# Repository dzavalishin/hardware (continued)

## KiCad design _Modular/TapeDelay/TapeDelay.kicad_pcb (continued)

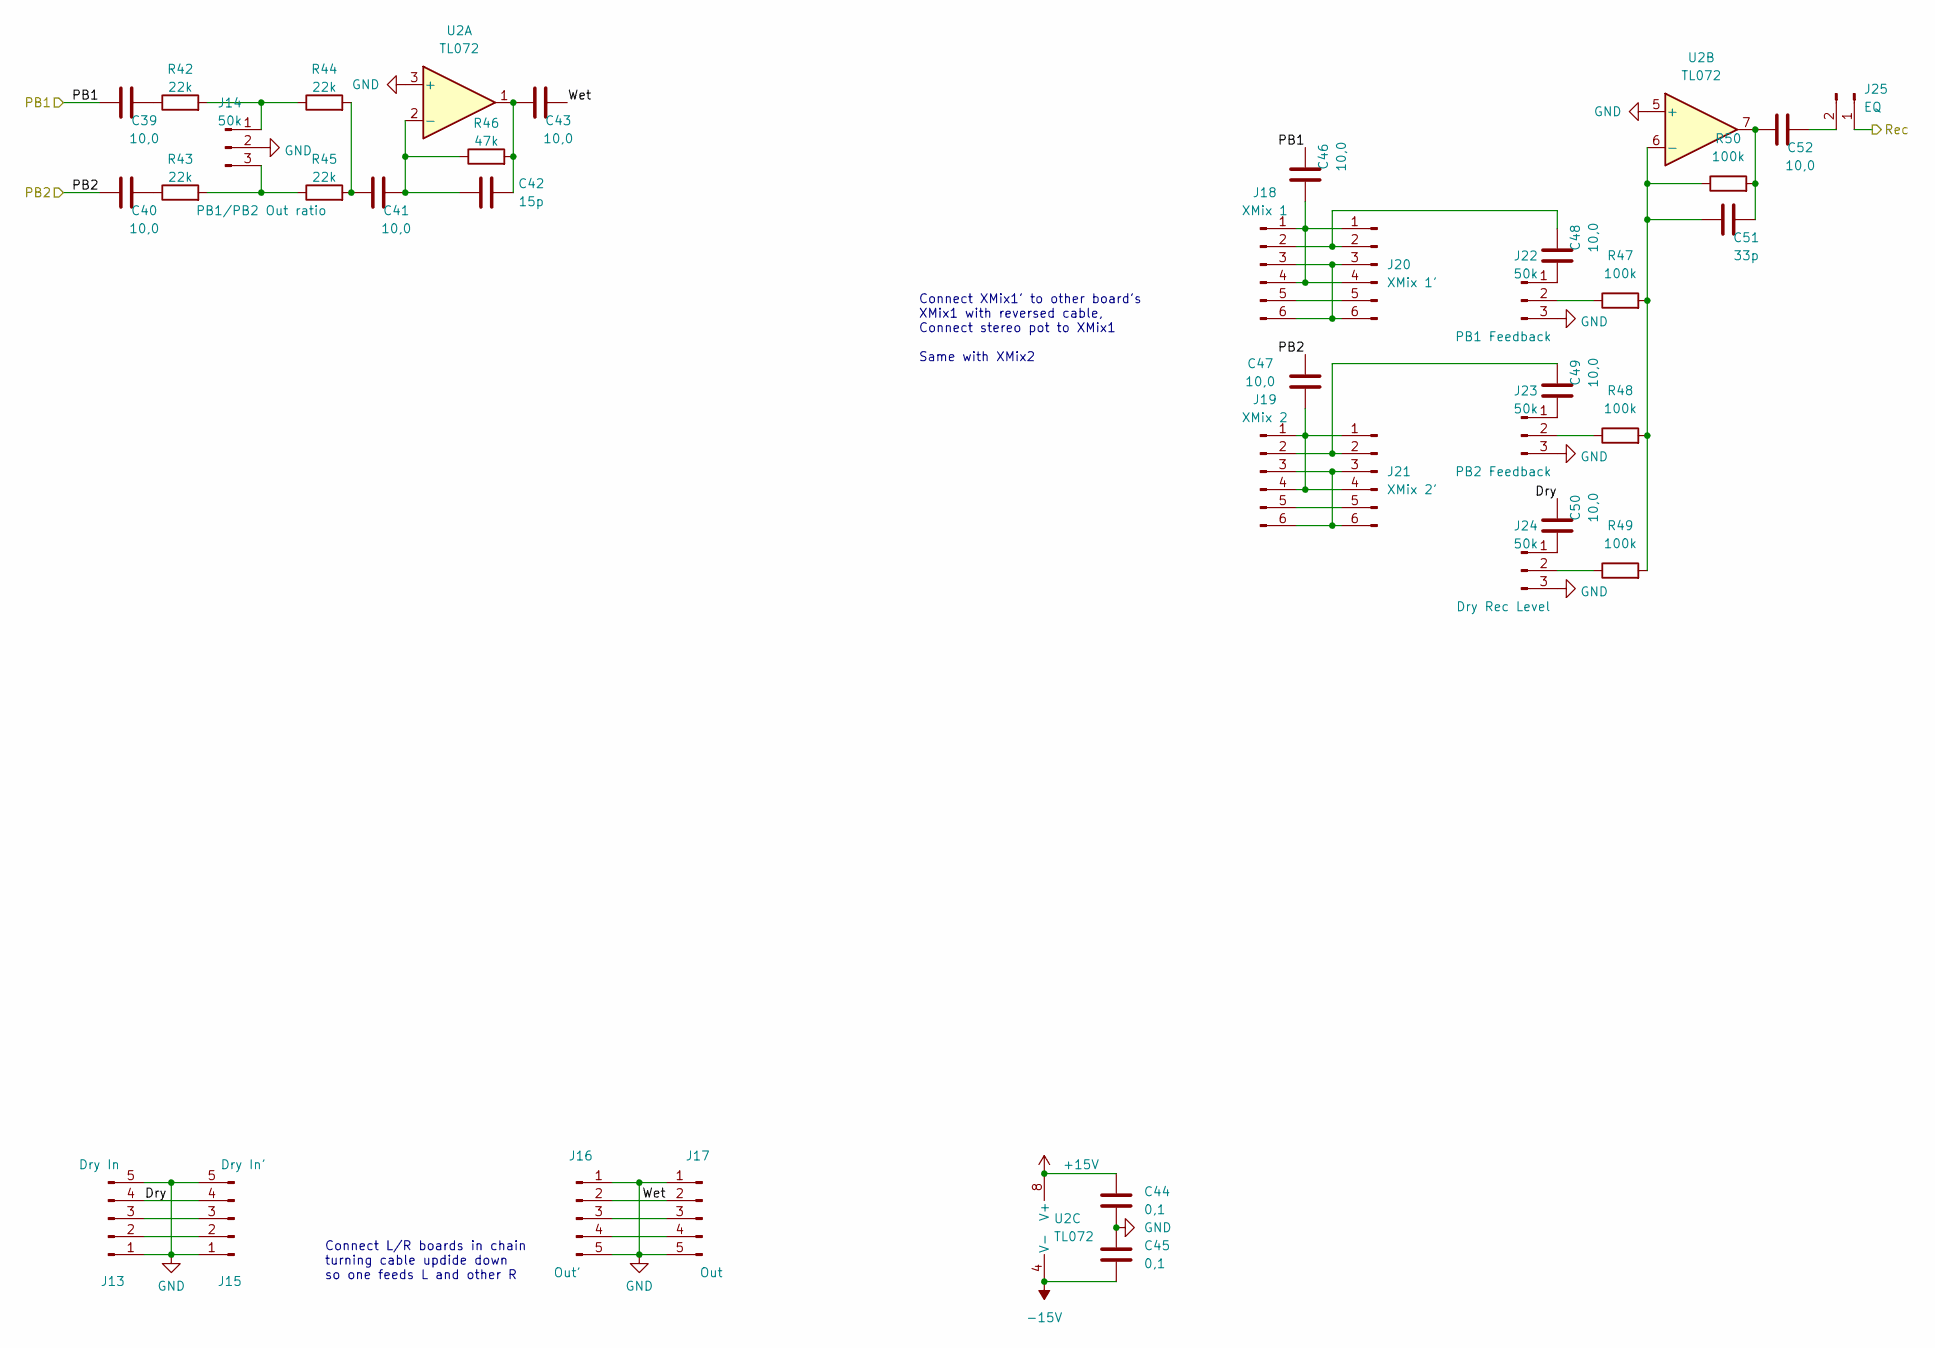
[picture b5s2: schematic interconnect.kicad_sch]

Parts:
C39, C40, C41: 10,0; C_0805_2012Metric_Pad1.18x1.45mm_HandSolder
C42: 15p; C_Disc_D5.0mm_W2.5mm_P2.50mm
C43, C46, C47, C48, C49, C50, C52: 10,0; C_1206_3216Metric_Pad1.33x1.80mm_HandSolder
C44, C45: 0,1; C_1206_3216Metric_Pad1.33x1.80mm_HandSolder
C51: 33p; C_Disc_D5.0mm_W2.5mm_P2.50mm
J13: Dry In; PinHeader_1x05_P2.54mm_Vertical
J14, J22, J23, J24: 50k; PinHeader_1x03_P2.54mm_Vertical
J15: Dry In'; PinHeader_1x05_P2.54mm_Vertical
J16: Out'; PinHeader_1x05_P2.54mm_Vertical
J17: Out; PinHeader_1x05_P2.54mm_Vertical
J18: XMix 1; PinHeader_1x06_P2.54mm_Vertical
J19: XMix 2; PinHeader_1x06_P2.54mm_Vertical
J20: XMix 1'; PinHeader_1x06_P2.54mm_Vertical
J21: XMix 2'; PinHeader_1x06_P2.54mm_Vertical
J25: EQ; PinHeader_1x02_P2.54mm_Vertical
R42, R43, R44, R45: 22k; R_1206_3216Metric_Pad1.30x1.75mm_HandSolder
R46: 47k; R_1206_3216Metric_Pad1.30x1.75mm_HandSolder
R47, R48, R49, R50: 100k; R_1206_3216Metric_Pad1.30x1.75mm_HandSolder
U2: TL072; DIP-8_W7.62mm_LongPads

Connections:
+15V: C44.1, U2.8 (V+); also elsewhere on the board
-15V: C45.2, U2.4 (V-); also elsewhere on the board
/Interconnect/Dry: C50.2, J13.4, J15.4
/Interconnect/Wet: C43.2, J16.2, J17.2
/PB1: C39.1, C46.2; also elsewhere on the board
/PB2: C40.1, C47.2; also elsewhere on the board
/Rec: J25.1; also elsewhere on the board
GND: C44.2, C45.1, J13.1, J13.5, J14.2, J15.1, J15.5, J16.1, J16.5, J17.1, J17.5, J22.3, J23.3, J24.3, U2.3 (+), U2.5 (+); also elsewhere on the board
unnamed: C39.2, R42.1
unnamed: C40.2, R43.1
unnamed: C41.1, R44.2, R45.2
unnamed: C41.2, C42.1, R46.1, U2.2 (-)
unnamed: C42.2, C43.1, R46.2, U2.1
unnamed: C46.1, J18.1, J18.4, J20.1, J20.4
unnamed: C47.1, J19.1, J19.4, J21.1, J21.4
unnamed: C48.1, J22.1
unnamed: C48.2, J18.2, J20.2
unnamed: C49.1, J23.1
unnamed: C49.2, J19.2, J21.2
unnamed: C50.1, J24.1
unnamed: C51.1, R47.2, R48.2, R49.2, R50.1, U2.6 (-)
unnamed: C51.2, C52.1, R50.2, U2.7
unnamed: C52.2, J25.2
unnamed: J13.2, J15.2
unnamed: J13.3, J15.3
unnamed: J14.1, R42.2, R44.1
unnamed: J14.3, R43.2, R45.1
unnamed: J16.3, J17.3
unnamed: J16.4, J17.4
unnamed: J18.3, J18.6, J20.3, J20.6
unnamed: J18.5, J20.5
unnamed: J19.3, J19.6, J21.3, J21.6
unnamed: J19.5, J21.5
unnamed: J22.2, R47.1
unnamed: J23.2, R48.1
unnamed: J24.2, R49.1

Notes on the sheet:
Connect L/R boards in chain turning cable updide down so one feeds L and other R
Connect XMix1' to other board's XMix1 with reversed cable, Connect stereo pot to XMix1 Same with XMix2

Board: 2 copper layers, 138 parts (84 on the bottom side), 95 nets, no tracks yet.

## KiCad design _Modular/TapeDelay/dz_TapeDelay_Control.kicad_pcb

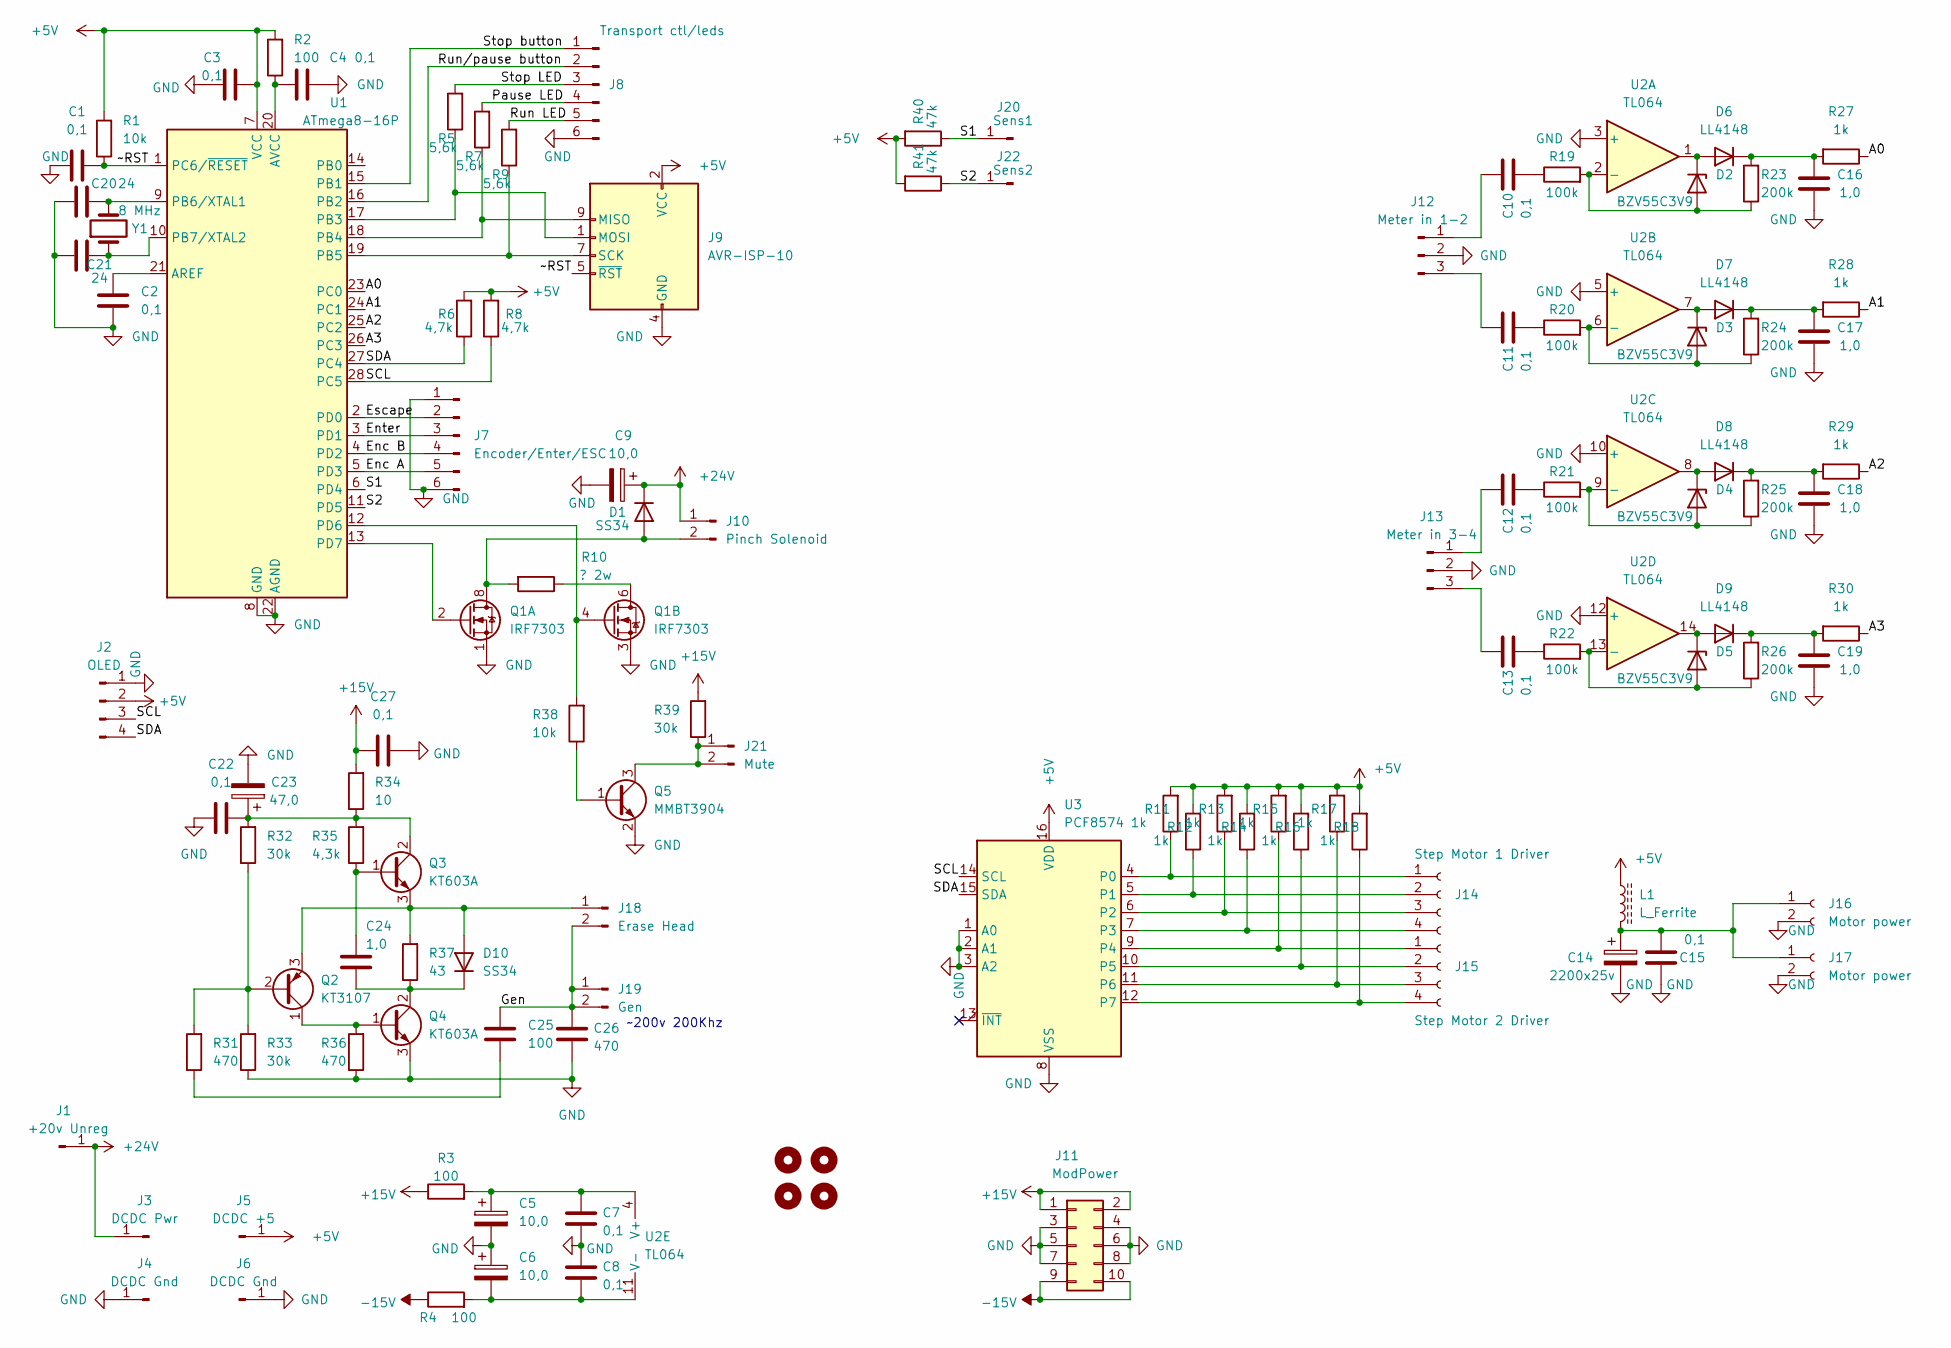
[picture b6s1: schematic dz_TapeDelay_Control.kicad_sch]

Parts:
C1, C2, C3, C4, C7, C8, C10, C11, C12, C13, C15: 0,1; C_1206_3216Metric_Pad1.33x1.80mm_HandSolder
C5, C6: 10,0; C_0805_2012Metric_Pad1.18x1.45mm_HandSolder
C9: 10,0; CP_Radial_D6.3mm_P2.50mm
C14: 2200x25v; CP_Radial_D13.0mm_P5.00mm
C16, C17, C18, C19, C24: 1,0; C_0805_2012Metric_Pad1.18x1.45mm_HandSolder
C20, C21: 24; C_Disc_D5.0mm_W2.5mm_P2.50mm
C22, C27: 0,1; C_0805_2012Metric_Pad1.18x1.45mm_HandSolder
C23: 47,0; CP_Radial_D6.3mm_P2.50mm
C25: 100; C_Disc_D5.0mm_W2.5mm_P2.50mm
C26: 470; C_Disc_D5.0mm_W2.5mm_P2.50mm
D1, D10: SS34; D_SMA-SMB_Universal_Handsoldering
D2, D3, D4, D5: BZV55C3V9; D_MiniMELF
D6, D7, D8, D9: LL4148; D_MiniMELF
H1, H2, H3, H4: MountingHole; MountingHole_3.2mm_M3
J1: +20v Unreg; PinHeader_1x01_P2.54mm_Vertical
J2: OLED; PinHeader_1x04_P2.54mm_Vertical
J3: DCDC Pwr; PinHeader_1x01_P2.54mm_Vertical
J4, J6: DCDC Gnd; PinHeader_1x01_P2.54mm_Vertical
J5: DCDC +5; PinHeader_1x01_P2.54mm_Vertical
J7: Encoder/Enter/ESC; PinHeader_1x06_P2.54mm_Vertical
J8: Transport ctl/leds; PinHeader_1x06_P2.54mm_Vertical
J9: AVR-ISP-10; PinHeader_2x05_P2.54mm_Vertical
J10: Pinch Solenoid; PinHeader_1x02_P2.54mm_Vertical
J11: ModPower; PinHeader_2x05_P2.54mm_Vertical
J12: Meter in 1-2; PinHeader_1x03_P2.54mm_Vertical
J13: Meter in 3-4; PinHeader_1x03_P2.54mm_Vertical
J14: Step Motor 1 Driver; PinHeader_1x04_P2.54mm_Vertical
J15: Step Motor 2 Driver; PinHeader_1x04_P2.54mm_Vertical
J16, J17: Motor power; PinHeader_1x02_P2.54mm_Vertical
J18: Erase Head; PinHeader_1x02_P2.54mm_Vertical
J19: Gen; PinHeader_1x02_P2.54mm_Vertical
J20: Sens1; PinHeader_1x01_P2.54mm_Vertical
J21: Mute; PinHeader_1x02_P2.54mm_Vertical
J22: Sens2; PinHeader_1x01_P2.54mm_Vertical
L1: L_Ferrite; L_Toroid_Vertical_L10.0mm_W5.0mm_P5.08mm
Q1: IRF7303; SOIC-8_3.9x4.9mm_P1.27mm
Q2: KT3107; TO-92
Q3, Q4: KT603A; TO-92_Wide
Q5: MMBT3904; SOT-23
R1, R38: 10k; R_1206_3216Metric_Pad1.30x1.75mm_HandSolder
R2, R3, R4: 100; R_1206_3216Metric_Pad1.30x1.75mm_HandSolder
R5, R7, R9: 5,6k; R_1206_3216Metric_Pad1.30x1.75mm_HandSolder
R6, R8: 4,7k; R_1206_3216Metric_Pad1.30x1.75mm_HandSolder
R10: ? 2w; R_Axial_DIN0309_L9.0mm_D3.2mm_P2.54mm_Vertical
R11, R12, R13, R14, R15, R16, R17, R18, R27, R28, R29, R30: 1k; R_1206_3216Metric_Pad1.30x1.75mm_HandSolder
R19, R20, R21, R22: 100k; R_1206_3216Metric_Pad1.30x1.75mm_HandSolder
R23, R24, R25, R26: 200k; R_1206_3216Metric_Pad1.30x1.75mm_HandSolder
R31, R36: 470; R_1206_3216Metric_Pad1.30x1.75mm_HandSolder
R32, R33, R39: 30k; R_1206_3216Metric_Pad1.30x1.75mm_HandSolder
R34: 10; R_Axial_DIN0309_L9.0mm_D3.2mm_P2.54mm_Vertical
R35: 4,3k; R_1206_3216Metric_Pad1.30x1.75mm_HandSolder
R37: 43; R_Axial_DIN0309_L9.0mm_D3.2mm_P2.54mm_Vertical
R40, R41: 47k; R_1206_3216Metric_Pad1.30x1.75mm_HandSolder
U1: ATmega8-16P; DIP-28_W7.62mm
U2: TL064; DIP-14_W7.62mm_LongPads
U3: PCF8574; DIP-16_W7.62mm_LongPads
Y1: 8 MHz; Crystal_HC49-U_Vertical

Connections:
+5V: C3.2, J2.2, J5.1, J9.2 (VCC), L1.1, R1.2, R2.2, R6.2, R8.2, R11.2, R12.2, R13.2, R14.2, R15.2, R16.2, R17.2, R18.2, R40.2, R41.2, U1.7 (VCC), U3.16 (VDD)
+15V: C27.2, J11.1, J11.2, R3.1, R34.2, R39.2
+24V: C9.1, D1.1 (K), J1.1, J3.1, J10.1
-15V: J11.9, J11.10, R4.1
/A0: R27.1, U1.23 (PC0)
/A1: R28.1, U1.24 (PC1)
/A2: R29.1, U1.25 (PC2)
/A3: R30.1, U1.26 (PC3)
/Enc A: J7.5, U1.5 (PD3)
/Enc B: J7.4, U1.4 (PD2)
/Enter: J7.3, U1.3 (PD1)
/Escape: J7.2, U1.2 (PD0)
/Gen: C25.2, C26.2, J18.2, J19.1, J19.2
/Pause LED: J8.4, R7.2
/Run LED: J8.5, R9.2
/Run/pause button: J8.2, U1.16 (PB2)
/S1: J20.1, R40.1, U1.6 (PD4)
/S2: J22.1, R41.1, U1.11 (PD5)
/SCL: J2.3, R8.1, U1.28 (PC5), U3.14 (SCL)
/SDA: J2.4, R6.1, U1.27 (PC4), U3.15 (SDA)
/Stop LED: J8.3, R5.2
/Stop button: J8.1, U1.15 (PB1)
/~RST: C1.2, J9.5 (~RST), R1.1, U1.1 (PC6/~RESET)
GND: C1.1, C2.2, C3.1, C4.2, C5.2, C6.1, C7.2, C8.1, C9.2, C14.2, C15.1, C16.1, C17.1, C18.1, C19.1, C20.2, C21.2, C22.2, C23.2, C26.1, C27.1, J2.1, J4.1, J6.1, J7.1, J7.6, J8.6, J9.4 (GND), J9.6 (GND), J9.8 (GND), J9.10 (GND), J11.3, J11.4, J11.5, J11.6, J11.7, J11.8, J12.2, J13.2, J16.2, J17.2, Q1.1 (S), Q1.3 (1), Q4.3 (E), Q5.2 (E), R33.1, R36.1, U1.8 (GND), U1.22 (AGND), U2.3 (+), U2.5 (+), U2.10 (+), U2.12 (+), U3.1 (A0), U3.2 (A1), U3.3 (A2), U3.8 (VSS)
unnamed: C2.1, U1.21 (AREF)
unnamed: C4.1, R2.1, U1.20 (AVCC)
unnamed: C5.1, C7.1, R3.2, U2.4 (V+)
unnamed: C6.2, C8.2, R4.2, U2.11 (V-)
unnamed: C10.1, J12.1
unnamed: C10.2, R19.1
unnamed: C11.1, J12.3
unnamed: C11.2, R20.1
unnamed: C12.1, J13.1
unnamed: C12.2, R21.1
unnamed: C13.1, J13.3
unnamed: C13.2, R22.1
unnamed: C14.1, C15.2, J16.1, J17.1, L1.2
unnamed: C16.2, D6.1 (K), R23.2, R27.2
unnamed: C17.2, D7.1 (K), R24.2, R28.2
unnamed: C18.2, D8.1 (K), R25.2, R29.2
unnamed: C19.2, D9.1 (K), R26.2, R30.2
unnamed: C20.1, U1.9 (PB6/XTAL1), Y1.2
unnamed: C21.1, U1.10 (PB7/XTAL2), Y1.1
unnamed: C22.1, C23.1, Q3.2 (C), R32.2, R34.1, R35.2
unnamed: C24.1, D10.1 (K), Q4.2 (C), R37.1
unnamed: C24.2, Q3.1 (B), R35.1
unnamed: C25.1, R31.1
unnamed: D1.2 (A), J10.2, Q1.7 (D), Q1.8 (D), R10.2
unnamed: D2.1 (K), D6.2 (A), U2.1
unnamed: D2.2 (A), R19.2, R23.1, U2.2 (-)
unnamed: D3.1 (K), D7.2 (A), U2.7
unnamed: D3.2 (A), R20.2, R24.1, U2.6 (-)
unnamed: D4.1 (K), D8.2 (A), U2.8
unnamed: D4.2 (A), R21.2, R25.1, U2.9 (-)
unnamed: D5.1 (K), D9.2 (A), U2.14
unnamed: D5.2 (A), R22.2, R26.1, U2.13 (-)
unnamed: D10.2 (A), J18.1, Q2.3 (E), Q3.3 (E), R37.2
unnamed: J9.1 (MOSI), R5.1, U1.17 (PB3)
unnamed: J9.7 (SCK), R9.1, U1.19 (PB5)
unnamed: J9.9 (MISO), R7.1, U1.18 (PB4)
unnamed: J14.1, R11.1, U3.4 (P0)
unnamed: J14.2, R12.1, U3.5 (P1)
unnamed: J14.3, R13.1, U3.6 (P2)
unnamed: J14.4, R14.1, U3.7 (P3)
unnamed: J15.1, R15.1, U3.9 (P4)
unnamed: J15.2, R16.1, U3.10 (P5)
unnamed: J15.3, R17.1, U3.11 (P6)
unnamed: J15.4, R18.1, U3.12 (P7)
unnamed: J21.1, J21.2, Q5.3 (C), R39.1
unnamed: Q1.2 (G), U1.13 (PD7)
unnamed: Q1.4 (G), R38.2, U1.12 (PD6)
unnamed: Q1.5 (D), Q1.6 (D), R10.1
unnamed: Q2.1 (C), Q4.1 (B), R36.2
unnamed: Q2.2 (B), R31.2, R32.1, R33.2
unnamed: Q5.1 (B), R38.1

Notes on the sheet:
~200v 200Khz

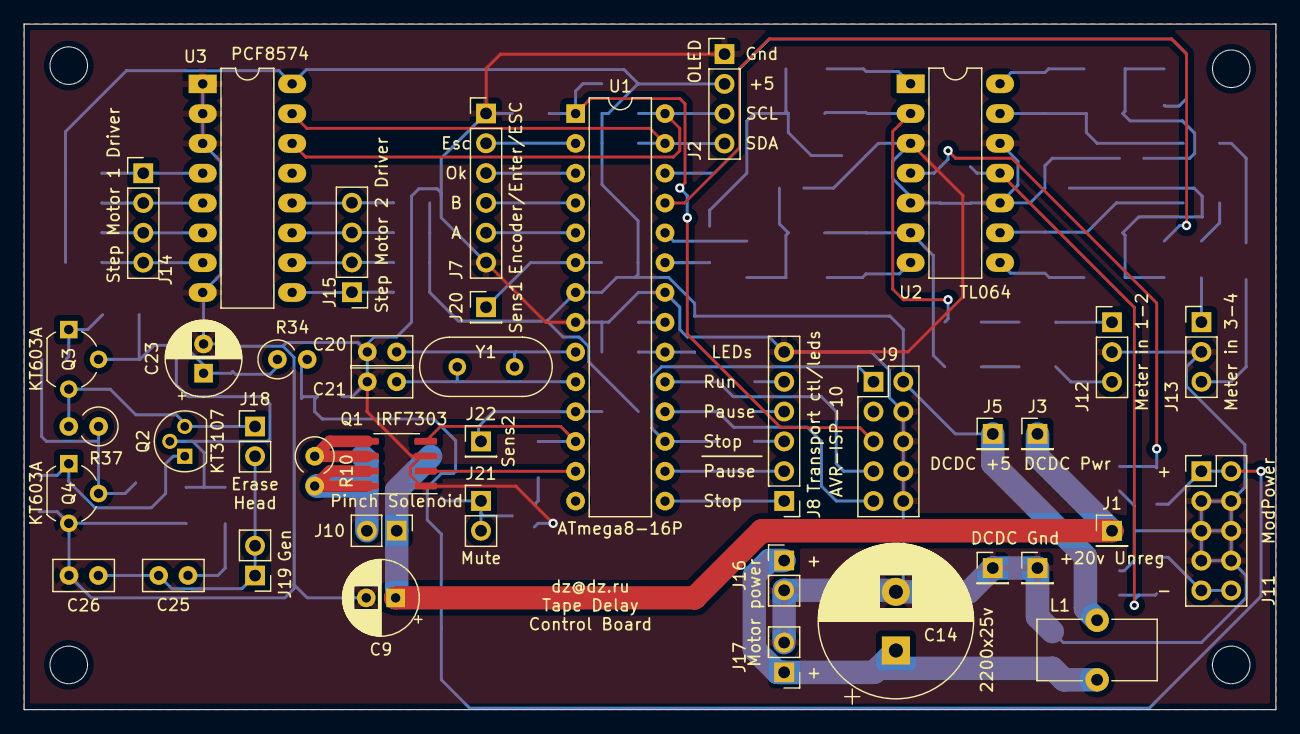
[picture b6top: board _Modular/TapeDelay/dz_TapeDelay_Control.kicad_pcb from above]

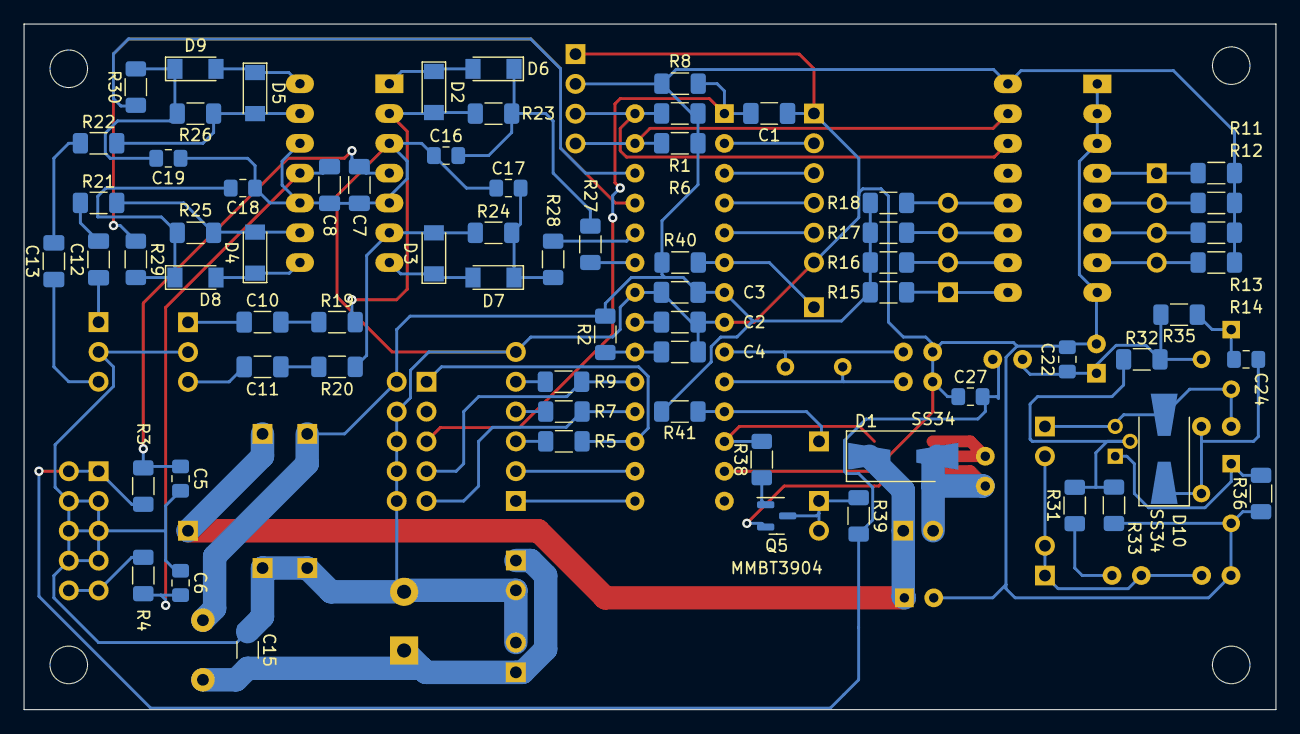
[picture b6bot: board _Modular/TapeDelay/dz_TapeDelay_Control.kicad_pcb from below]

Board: 2 copper layers, 106.7 x 58.4 mm, 114 parts (69 on the bottom side), 75 nets.

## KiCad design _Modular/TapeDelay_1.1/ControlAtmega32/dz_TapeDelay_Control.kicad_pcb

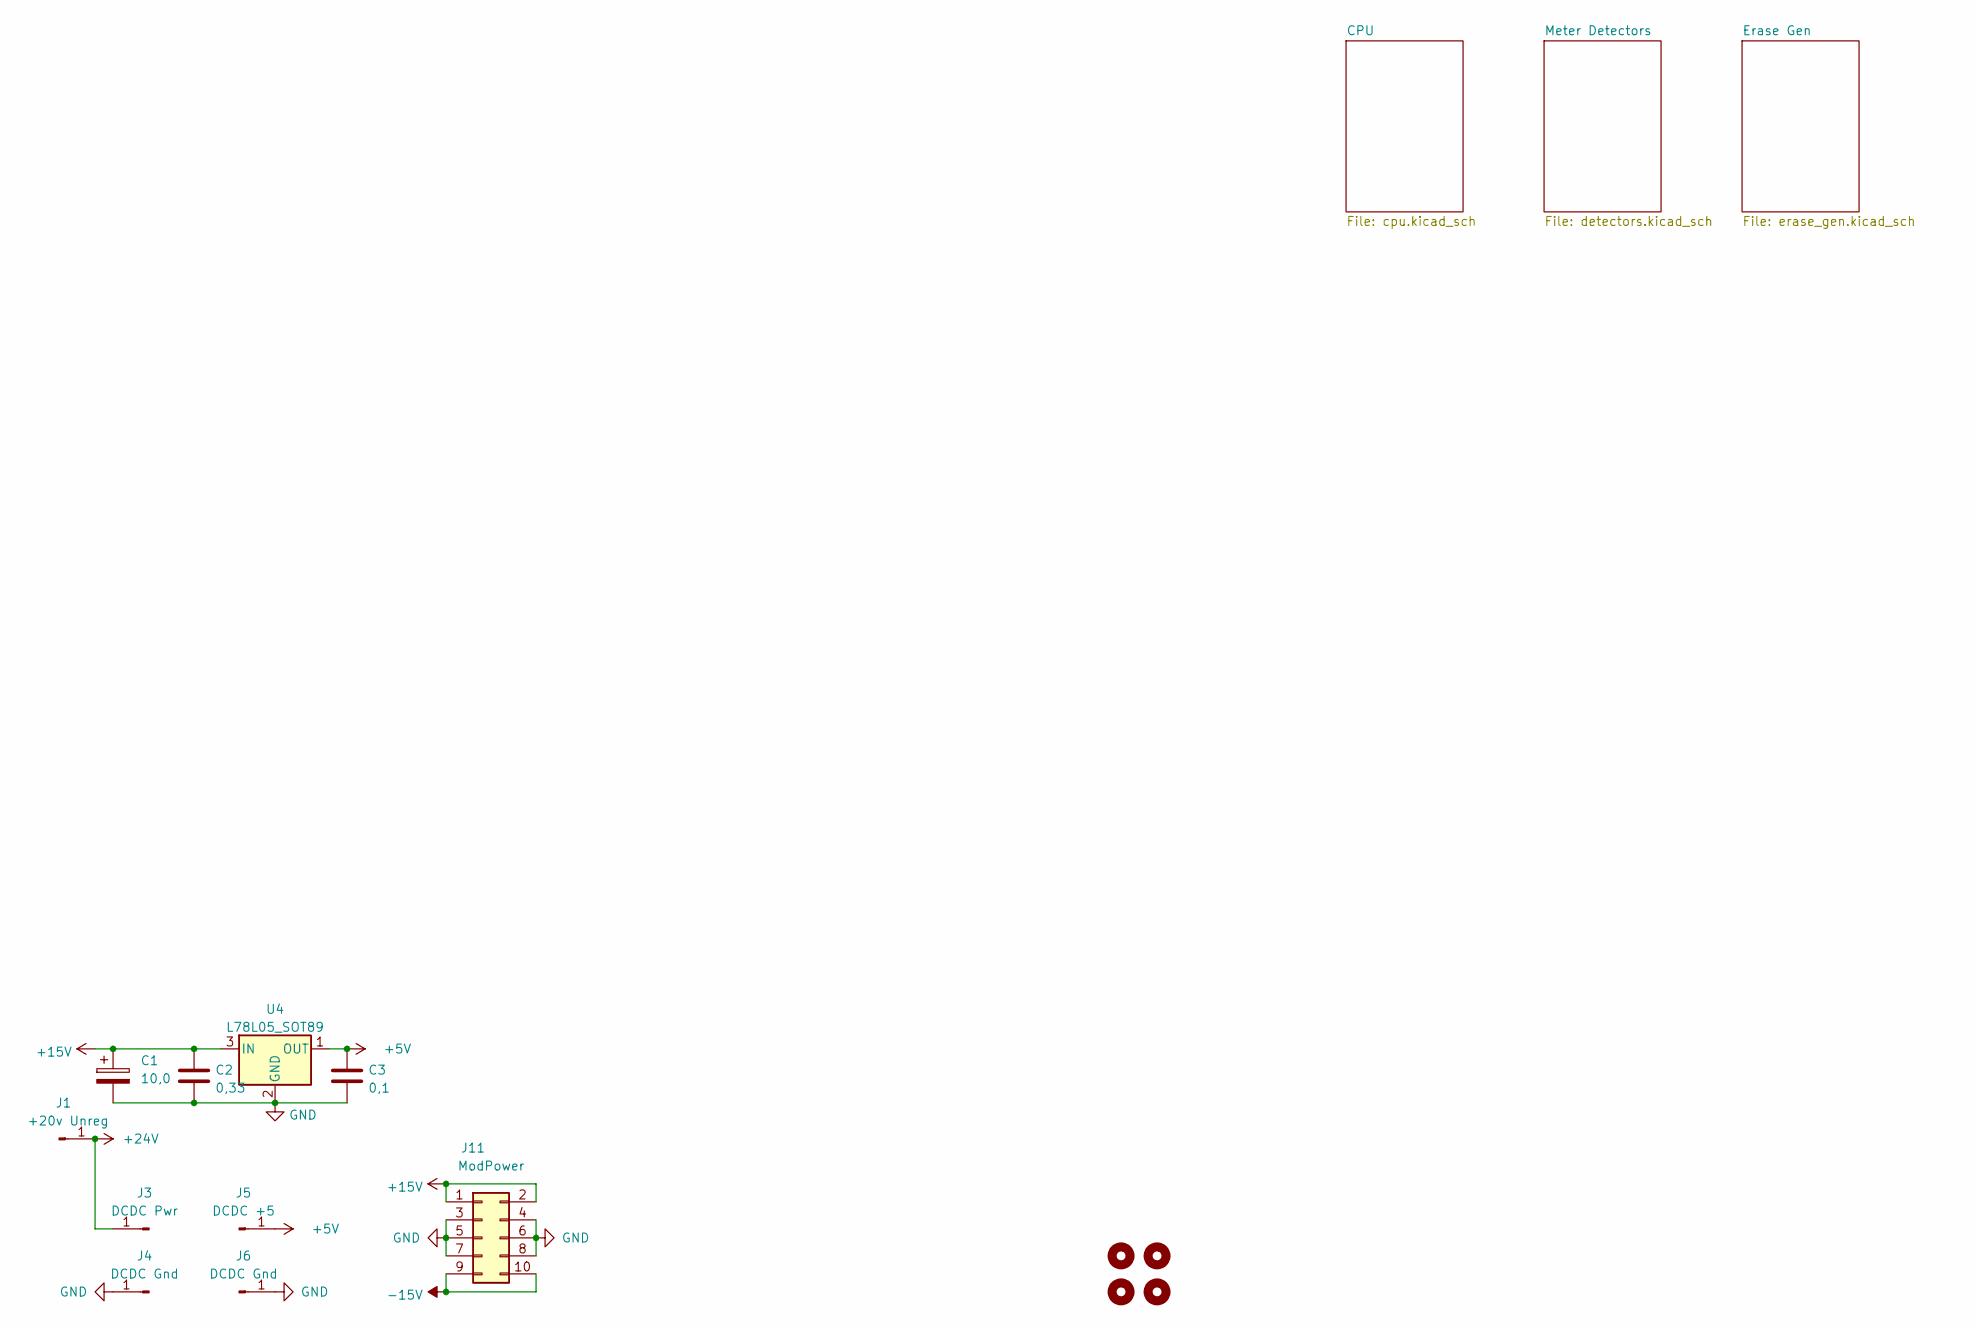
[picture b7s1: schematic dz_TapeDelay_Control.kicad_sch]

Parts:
C1: 10,0; C_0805_2012Metric_Pad1.18x1.45mm_HandSolder
C2: 0,33; C_1206_3216Metric_Pad1.33x1.80mm_HandSolder
C3: 0,1; C_1206_3216Metric_Pad1.33x1.80mm_HandSolder
H1, H2, H3, H4: MountingHole; MountingHole_3.2mm_M3
J1: +20v Unreg; PinHeader_1x01_P2.54mm_Vertical
J3: DCDC Pwr; PinHeader_1x01_P2.54mm_Vertical
J4, J6: DCDC Gnd; PinHeader_1x01_P2.54mm_Vertical
J5: DCDC +5; PinHeader_1x01_P2.54mm_Vertical
J11: ModPower; PinHeader_2x05_P2.54mm_Vertical
U4: L78L05_SOT89; SOT-89-3

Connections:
+5V: C3.1, J5.1, U4.1 (OUT); also elsewhere on the board
+15V: C1.1, C2.1, J11.1, J11.2, U4.3 (IN); also elsewhere on the board
+24V: J1.1, J3.1
-15V: J11.9, J11.10; also elsewhere on the board
GND: C1.2, C2.2, C3.2, J4.1, J6.1, J11.3, J11.4, J11.5, J11.6, J11.7, J11.8, U4.2 (GND); also elsewhere on the board

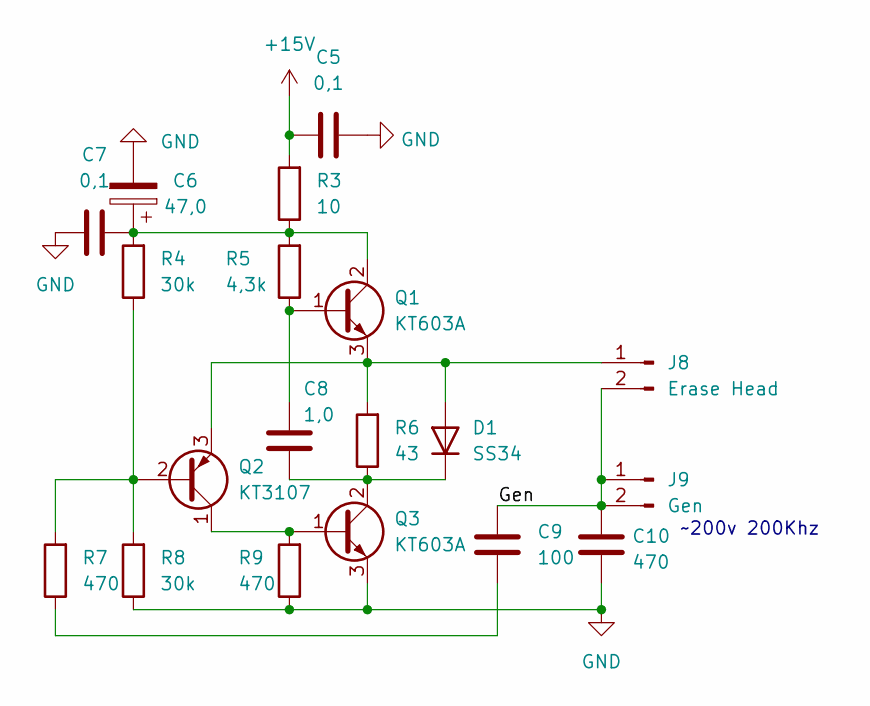
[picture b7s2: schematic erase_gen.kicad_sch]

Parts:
C5, C7: 0,1; C_0805_2012Metric_Pad1.18x1.45mm_HandSolder
C6: 47,0; CP_Radial_D6.3mm_P2.50mm
C8: 1,0; C_0805_2012Metric_Pad1.18x1.45mm_HandSolder
C9: 100; C_Disc_D5.0mm_W2.5mm_P2.50mm
C10: 470; C_Disc_D5.0mm_W2.5mm_P2.50mm
D1: SS34; D_SMA-SMB_Universal_Handsoldering
J8: Erase Head; PinHeader_1x02_P2.54mm_Vertical
J9: Gen; PinHeader_1x02_P2.54mm_Vertical
Q1, Q3: KT603A; TO-92_Wide
Q2: KT3107; TO-92
R3: 10; R_Axial_DIN0309_L9.0mm_D3.2mm_P2.54mm_Vertical
R4, R8: 30k; R_1206_3216Metric_Pad1.30x1.75mm_HandSolder
R5: 4,3k; R_1206_3216Metric_Pad1.30x1.75mm_HandSolder
R6: 43; R_Axial_DIN0309_L9.0mm_D3.2mm_P2.54mm_Vertical
R7, R9: 470; R_1206_3216Metric_Pad1.30x1.75mm_HandSolder

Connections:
+15V: C5.2, R3.2; also elsewhere on the board
/Erase Gen/Gen: C9.2, C10.2, J8.2, J9.1, J9.2
GND: C5.1, C6.2, C7.2, C10.1, Q3.3 (E), R8.1, R9.1; also elsewhere on the board
unnamed: C6.1, C7.1, Q1.2 (C), R3.1, R4.2, R5.2
unnamed: C8.1, D1.1 (K), Q3.2 (C), R6.1
unnamed: C8.2, Q1.1 (B), R5.1
unnamed: C9.1, R7.1
unnamed: D1.2 (A), J8.1, Q1.3 (E), Q2.3 (E), R6.2
unnamed: Q2.1 (C), Q3.1 (B), R9.2
unnamed: Q2.2 (B), R4.1, R7.2, R8.2

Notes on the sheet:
~200v 200Khz

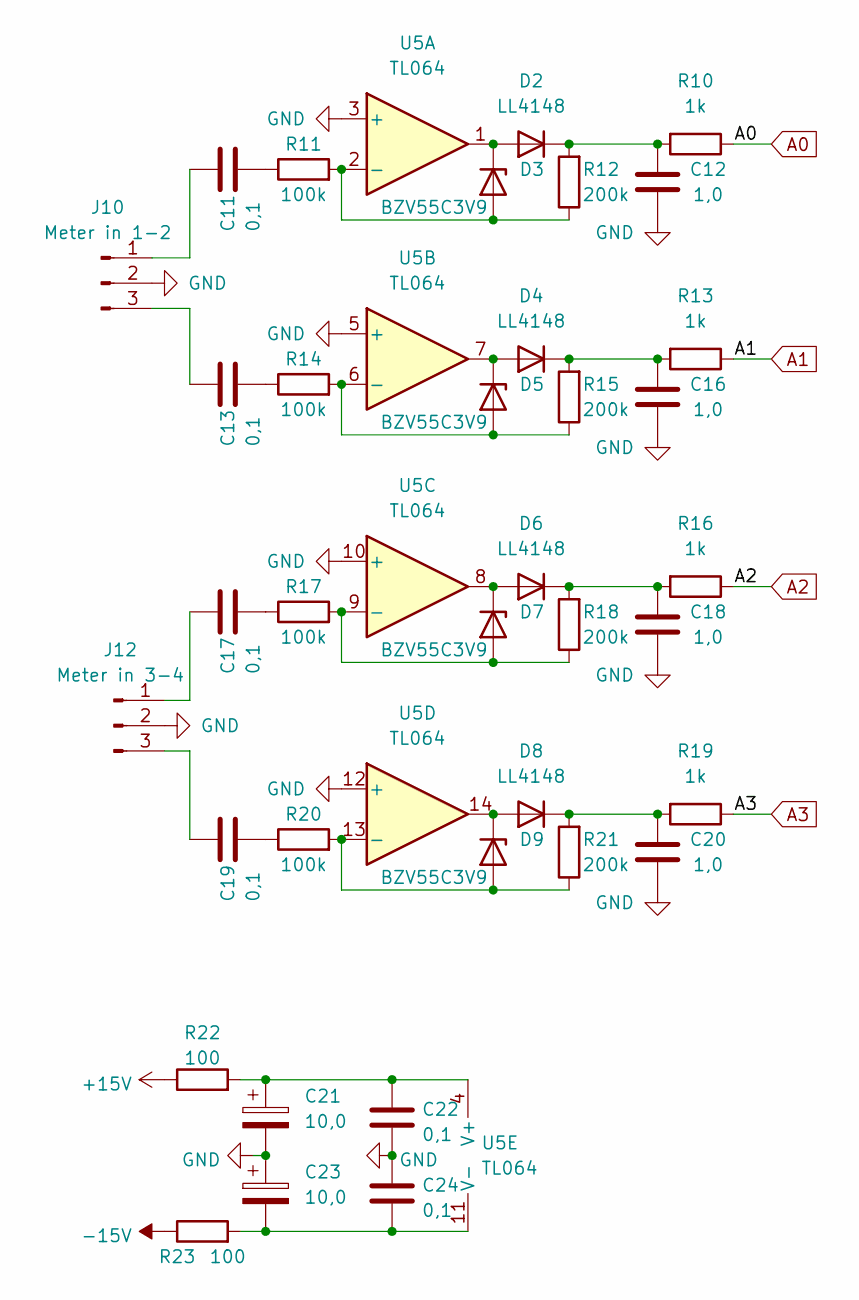
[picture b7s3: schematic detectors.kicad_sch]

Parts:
C11, C13, C17, C19, C22, C24: 0,1; C_1206_3216Metric_Pad1.33x1.80mm_HandSolder
C12, C16, C18, C20: 1,0; C_0805_2012Metric_Pad1.18x1.45mm_HandSolder
C21, C23: 10,0; C_0805_2012Metric_Pad1.18x1.45mm_HandSolder
D2, D4, D6, D8: LL4148; D_MiniMELF
D3, D5, D7, D9: BZV55C3V9; D_MiniMELF
J10: Meter in 1-2; PinHeader_1x03_P2.54mm_Vertical
J12: Meter in 3-4; PinHeader_1x03_P2.54mm_Vertical
R10, R13, R16, R19: 1k; R_1206_3216Metric_Pad1.30x1.75mm_HandSolder
R11, R14, R17, R20: 100k; R_1206_3216Metric_Pad1.30x1.75mm_HandSolder
R12, R15, R18, R21: 200k; R_1206_3216Metric_Pad1.30x1.75mm_HandSolder
R22, R23: 100; R_1206_3216Metric_Pad1.30x1.75mm_HandSolder
U5: TL064; DIP-14_W7.62mm_Socket_LongPads

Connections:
+15V: R22.1; also elsewhere on the board
-15V: R23.1; also elsewhere on the board
A0: R10.1; also elsewhere on the board
A1: R13.1; also elsewhere on the board
A2: R16.1; also elsewhere on the board
A3: R19.1; also elsewhere on the board
GND: C12.1, C16.1, C18.1, C20.1, C21.2, C22.2, C23.1, C24.1, J10.2, J12.2, U5.3 (+), U5.5 (+), U5.10 (+), U5.12 (+); also elsewhere on the board
unnamed: C11.1, J10.1
unnamed: C11.2, R11.1
unnamed: C12.2, D2.1 (K), R10.2, R12.2
unnamed: C13.1, J10.3
unnamed: C13.2, R14.1
unnamed: C16.2, D4.1 (K), R13.2, R15.2
unnamed: C17.1, J12.1
unnamed: C17.2, R17.1
unnamed: C18.2, D6.1 (K), R16.2, R18.2
unnamed: C19.1, J12.3
unnamed: C19.2, R20.1
unnamed: C20.2, D8.1 (K), R19.2, R21.2
unnamed: C21.1, C22.1, R22.2, U5.4 (V+)
unnamed: C23.2, C24.2, R23.2, U5.11 (V-)
unnamed: D2.2 (A), D3.1 (K), U5.1
unnamed: D3.2 (A), R11.2, R12.1, U5.2 (-)
unnamed: D4.2 (A), D5.1 (K), U5.7
unnamed: D5.2 (A), R14.2, R15.1, U5.6 (-)
unnamed: D6.2 (A), D7.1 (K), U5.8
unnamed: D7.2 (A), R17.2, R18.1, U5.9 (-)
unnamed: D8.2 (A), D9.1 (K), U5.14
unnamed: D9.2 (A), R20.2, R21.1, U5.13 (-)
